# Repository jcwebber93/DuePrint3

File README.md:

# DuePrint3
Duet 3 to Stratasys PDB Interface Board. Used to convert a Stratasys Prodigy series printer (Dimension, uPrint, Fortus 250) to use a modern control board & firmware. This conversion is fully reversable (assuming the printer functions to begin with). Many thanks to AJ Quick and Archeantus (Jeremy) for their past efforts in detailing the electronics of the Dimension/uPrint machines, as well as sharing details on their Duet 2 WiFi conversions.
* https://wiki.cnc.xyz/Stratasys_uPrint_Retrofit
* https://forum.duet3d.com/topic/12647/another-stratasys-uprint-retrofit

[Additional details for this project on the Duet3D forums.](https://forum.duet3d.com/topic/37434/dueprint-with-a-duet-3-6hc-stratasys-dimension-conversion)

At present, the implementation focuses on the Dimension 1200es printers (the implementations linked above focus on the uPrint series, which is quite similar. The electronics are laid out a touch differently, meaning the layout of the new hardware must change, as well where the stepper motor wiring taps in to the existing harness). The Duet 3 Mainboard 6HC, as well as the DP3EXB module (natively running RepRapFirmware/Duet3Expansion) interface with 17 inputs, and 11 outputs.
### Inputs
|Device|RRF Pin Name|Function|Gcode|Dependancy|Note|
|---|---|---|---|---|---|
|6HC HEADER 7|io2.in|PRINT BED TOUCH PR LIM SW|`M558 P5 H5 F1200:200 T18000 A3 C"!io2.in" ; Z probe`||Used for Z probing|
|6HC HEADER 9|io6.in|Z-AXIS EOT|`M574 Z2 S1 P"!io6.in" ; Z EOT to Z endstop on high side`||Remapped as part of Z homing routine|
|6HC HEADER 11|io4.in|Y-AXIS EOT|`M950 J6 C"!io4.in" ; Y EOT (High, Back)`||Used for Y end of travel (high side, back of printer)|
|6HC HEADER 13|io3.in|X-AXIS EOT|`M950 J5 C"!io3.in" ; X EOT (High)`||Used for X end of travel|
|6HC HEADER 15|io0.in|X-AXIS HOME SW|`M574 X1 S1 P"!io0.in" ; X home limit (low side)`||Used for X homing (low side)|
|6HC HEADER 17|io1.in|Y-AXIS HOME SW|`M574 Y1 S1 P"!io1.in" ; Y home limit (low side, front of printer)`||Used for Y homing (low side, front of printer)|
|6HC HEADER 19|io5.in|Z-AXIS HOME SW|`M950 J7 C"!io5.in" ; Z Home`||Remapped as part of Z homing routine|
|6HC HEADER 21|io8.in|POWER I/O|`M950 J11 C"io8.in" ; Power Switch Status`||Front power switch status|
|6HC HEADER 23|io7.in|PRINT HEAD TEMP ALARM|`M950 J9 C"!io7.in" ; Print Head Temp Alarm`||Print head temperature alarm|
|DP3EXB |PA07|CHAMBER TEMP ALARM|`M950 J10 C"124.pa07" ; Chamber Temp Alarm`||Chamber temperature alarm|
|DP3EXB |PA06|HEAD THERMOSTAT STATUS|`M950 J1 C"124.pa06" ; Head Thermostat`||Head thermostat|
|DP3EXB |PA05|DOOR SWITCH|`M950 J2 C"124.pa05" ; Door Status`||Door switch status|
|DP3EXB |PA04|SUPPORT TOGGLE SW|`M950 J3 C"124.pa04" ; T1 Toggle`||T1 (Support) toggle sensor|
|DP3EXB |PB11|MODEL TOGGLE SW|`M950 J4 C"124.pb08" ; T0 toggle`||T0 (Model) toggle sensor|
|6HC HEADER 18&20|temp0&VSSA|CHAMBER THERM|`M308 S0 A"Chamber" P"temp0" Y"linear-analog" F0 B-42 C113 ; Chamber Temp Sensor`||Chamber temperature sensor|
|6HC HEADER 22&24|temp2&VSSA|SUPPORT THERM|`M308 S1 A"Model" P"temp1" Y"linear-analog" F0 B12.5 C328 ; T1 (Support) Temp Sensor`||Tool 1 (Support) temperature sensor|
|6HC HEADER 26&28|temp1&VSSA|MODEL THERM|`M308 S2 A"Support" P"temp2" Y"linear-analog" F0 B12.5 C328 ; T0 (Model) Temp Sensor`||Tool 0 (Model) temperature sensor|

### Outputs
|Device|RRF Pin Name|Function|Gcode|Dependancy|Note|
|---|---|---|---|---|---|
|6HC HEADER 2|io0.out|120V ON|`M950 P5 C"io0.out" ; 120V On`|Outputs need to be enabled via "M42 P7 S0"|Enables 120V power supplies|
|6HC HEADER 3|out4|48V RTN|`M950 P7 C"!out4"  ; Disable Outputs`||This provides power to DuePrint3 level shifters.|
|6HC HEADER 4|io1.out|POWER ON|`M950 P6 C"io1.out" ; Controlled Shutdown`|Outputs need to be enabled via "M42 P7 S0"|When enabled, allows the printer to handle a controlled shutdown when front power switch is toggled|
|6HC HEADER 6|io3.out|MOTOR ENA|`M950 P1 C"io3.out" ;Extruder Motor`|Outputs need to be enabled via "M42 P7 S0"|Enables the extruder motor|
|6HC HEADER 8|io4.out|CHAMBER HEATER ENA|`M950 H0 C"io4.out" T0 ; Chamber heater, Sensor 0`|Outputs need to be enabled via "M42 P7 S0"|Chamber heater|
|6HC HEADER 10|io2.out|BLOWER ENA|`M950 P0 C"io2.out" ; Head Blower Fan`|Outputs need to be enabled via "M42 P7 S0"|Used to enable or disable head blower fan|
|6HC HEADER 12|io7.out|SUPPORT HEATER ENA|`M950 H2 C"io7.out" T2 ; T1 heater, Sensor 2`|Outputs need to be enabled via "M42 P7 S0"|Tool 1 (Support) heater|
|6HC HEADER 14|io5.out|EXTRUDER MODEL HEATER ENA|`M950 H1 C"io5.out" T1 ; T0 heater, Sensor 1`|Outputs need to be enabled via "M42 P7 S0"|Tool 0 (Model) heater|
|6HC HEADER 16|io6.out|DOOR SOLENOID ENA|`M950 P3 C"io6.out" ; Door Lock`|Outputs need to be enabled via "M42 P7 S0"|Used to enable or disable the door lock|
|DP3EXB |PA08|LED LIGHTS ENA|`M950 P4 C"124.pa24" ; Chamber Lights`||Used to enable or disable chamber lights|
|DP3EXB |PA10|PRINT BED TOUCH PR ENA|`M950 P2 C"124.pa25" ;Doesn't seem to function?`||Does not seem to have a function|

### Other
|Header Pin|Desc.|Label|
|---|---|---|
|6HC HEADER 1|N/A|NC|
|6HC HEADER 5|N/A|48V|
|6HC HEADER 25|N/A|NC|
|6HC HEADER 27|N/A|5V|
|6HC HEADER 29|N/A|GND|
|6HC HEADER 30|N/A|GND|

### Spares Header
|Header Pin|Desc.|Label|
|---|---|---|
|SPARE 1||GND|
|SPARE 2|PA27|SPR4|
|SPARE 3|PA02|SPR1|
|SPARE 4|PA23|SPR3|
|SPARE 5|PA01|SPR2|
|SPARE 6|PA19|I_SPR2|
|SPARE 7|PA12|I_SPR1|
|SPARE 8|PA17|SPR5|
|SPARE 9||5V|
|SPARE 10|PA09|SPR6|
|SPARE 11||GND|
|SPARE 12|PA11|SPR7|
|SPARE 13||12V|
|SPARE 14|PA18|SPR8|

The 6HC directly drives the X, Y, and Z stepper motors (vs. controlling them through the Stratasys PDB). The 6HC, unlike the Duet2 (and Duex boards) does not natively have STEP/DIR pins used to emit step and direction pulses. Instead, a DP3EXB expansion board running a fork of Duet3Expansion is used to natively control the extruder's closed loop DC motor. The extruder can be tuned via the ClosedLoopTuning plugin for DWC, with the motor parameters being configured in Config.g. RRF is able to monitor the motor for position errors.

## Materials
[A detailed BOM can be found here](https://github.com/jcwebber93/DuePrint3/blob/v2.5.0/DuePrint3%20BOM.xlsx), with the approximate cost being ~$660 (60% of this is Duet3D 6HC, DP3EXB Module, and DuetScreen).

## Interface Board Design
[The KidCad project for the DuePrint3 board can be found here](https://github.com/jcwebber93/DuePrint3/tree/v2.5.0/DuePrint3%20KiCad%20Project)

## Wiring
[A detailed wire list can be found here.](https://github.com/jcwebber93/DuePrint3/blob/v2.5.0/DuePrint3%20Wire%20List.xlsx) Connectors & crimps for the Duet 3 6HC are supplied with the board, but are JST VH (stepper motors) and Molex KK / Wurth WR-WTB (Wurth connectors/contacts are supplied with Duet Boards). The interface board 6HC and spares header are JST PHD, and spare 5v and 12v headers are Molex Micro-3.0 series connectors & crimps. The headers for the PBD ribbon cables are Samtec EHT series headers.

## DP3EXB Prep
DP3EXB prep to detailed

## Interface Board Prep
If the Interface Board (w/Sammy-C21) is the only CAN-FD device, aside from the Duet 3 6HC, place a 2-socket jumper on J13 as indicated to enable the CAN-FD termination resistor.

J11 connects to the 6HC. J12 can be used with additional expansion boards (such as a Duet 3 SZP on the print head, which could be used as an accelerometer or for bed scanning), provided the CAN-FD bus is terminated on the additional board.

## RepRapFirmware Prep
At present, the 6HC and DP3EXB are running a fork of 3.6.3 (to be documented). [Configuration files are located here](https://github.com/jcwebber93/DuePrint3/tree/v2.0.0/Duet%203%20Configuration/System%20Directory), and [Macros are located here.](https://github.com/jcwebber93/DuePrint3/tree/v2.0.0/Duet%203%20Configuration/Macros%20Directory)

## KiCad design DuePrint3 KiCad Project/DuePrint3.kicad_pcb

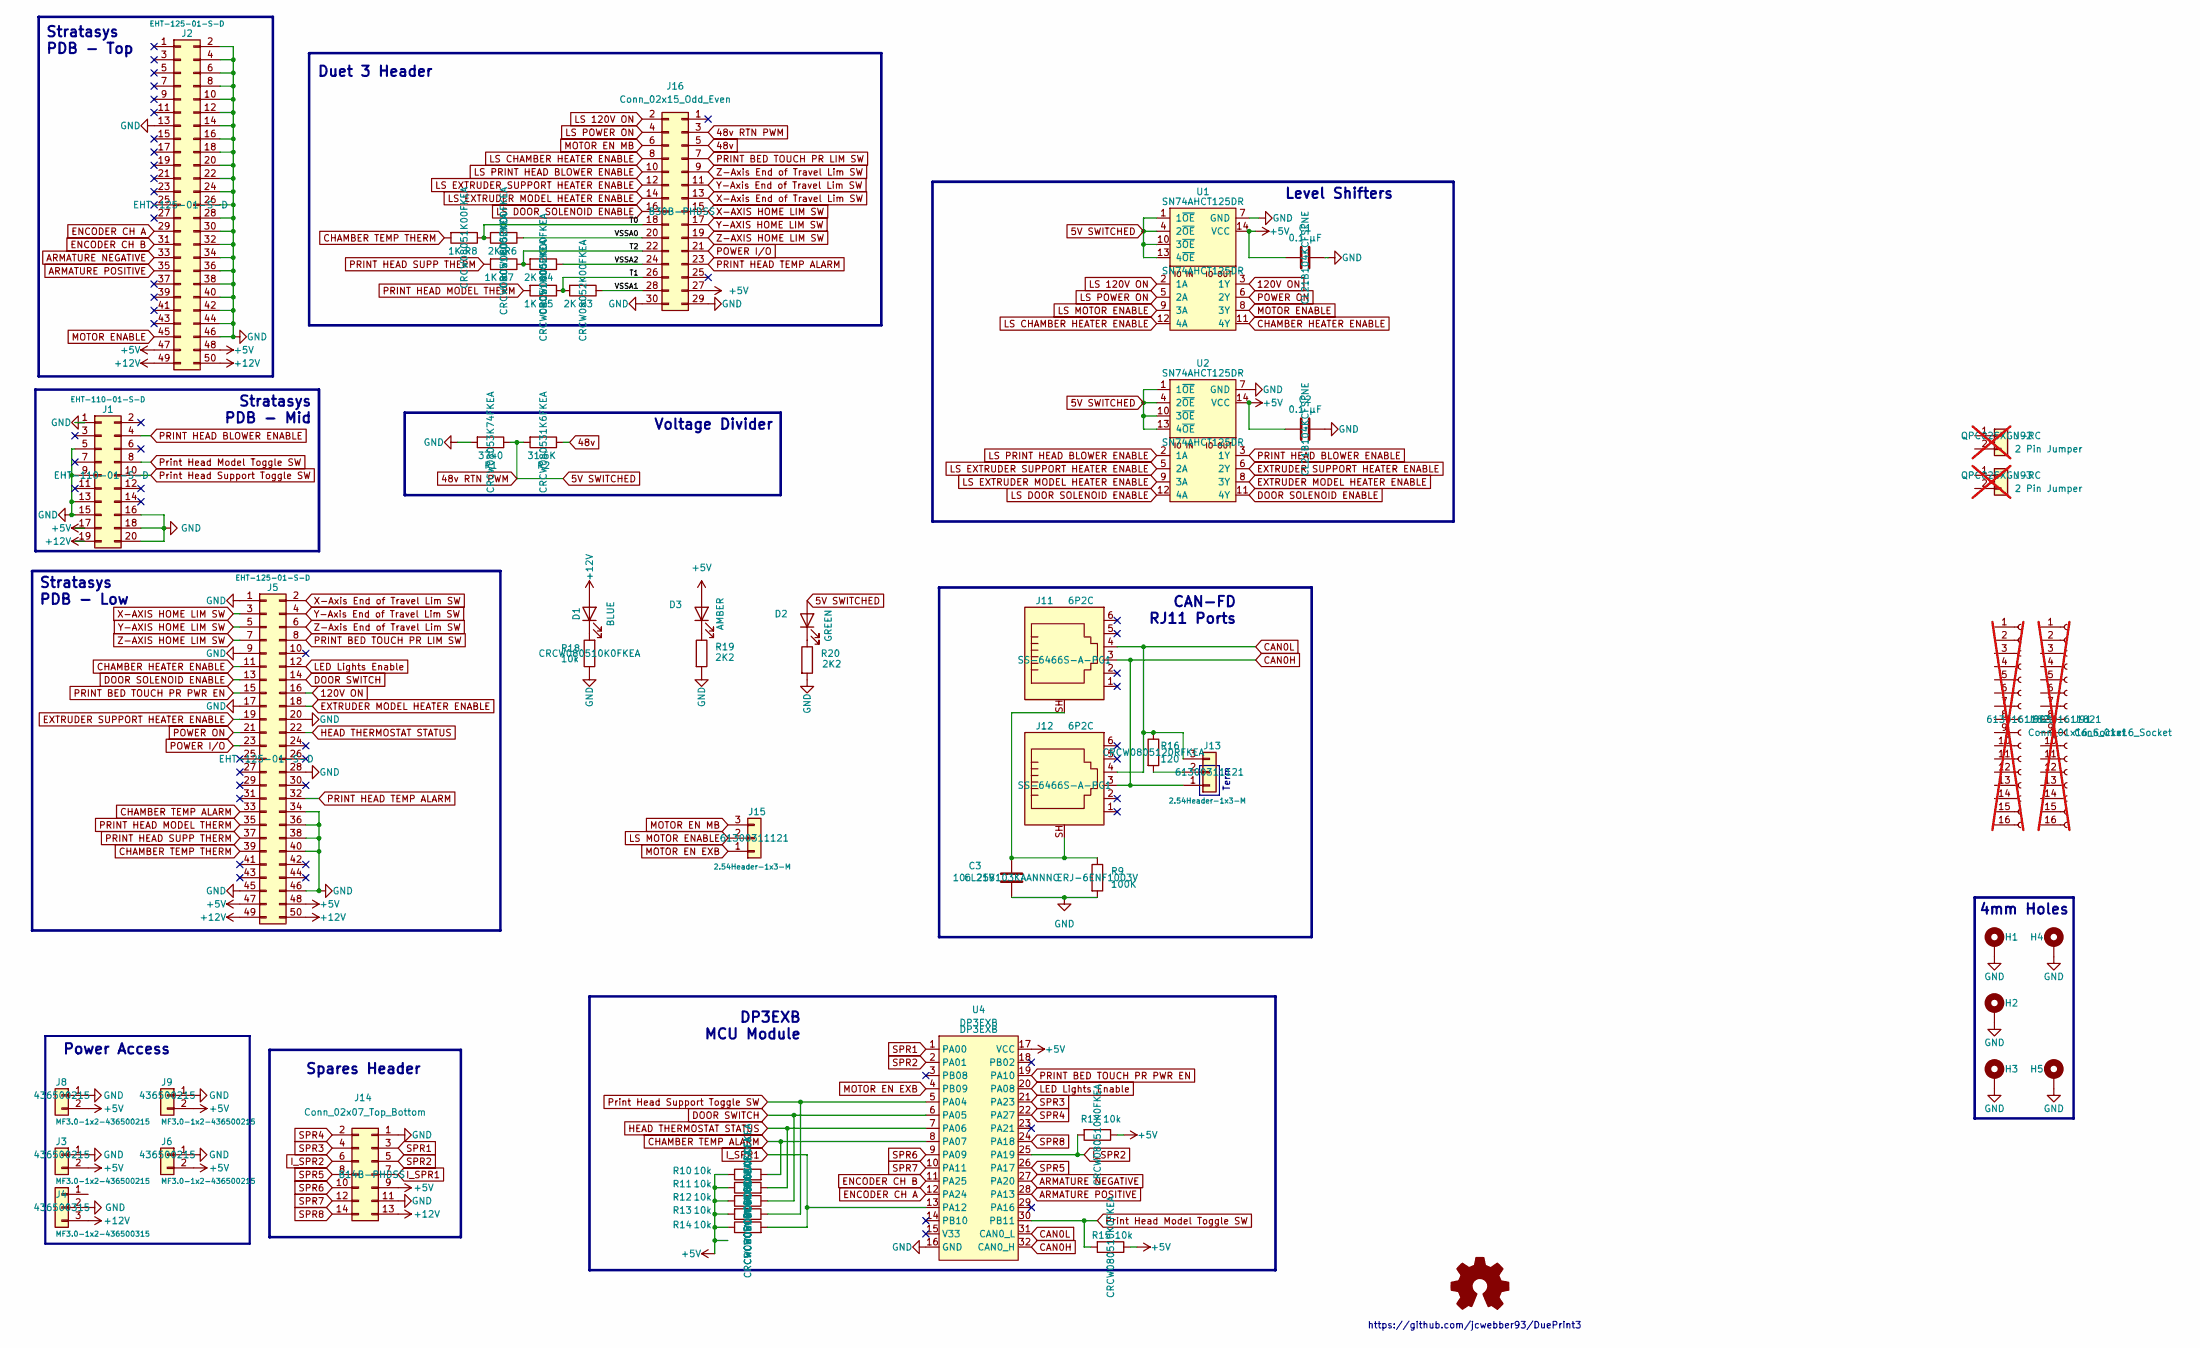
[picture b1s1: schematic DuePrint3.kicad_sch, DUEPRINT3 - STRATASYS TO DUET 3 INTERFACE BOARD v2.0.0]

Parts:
C1, C2: 0.1 µF; C_0805_2012Metric_Pad1.18x1.45mm_HandSolder; Part Number CL21B104KCFSFNE
C3: 10n 25V; C_0805_2012Metric_Pad1.18x1.45mm_HandSolder; Part Number CL21B103KAANNNC
D1: 12V; LED_0805_2012Metric_Pad1.15x1.40mm_HandSolder; Part Number 150080BS75000
D2: 5V_SW; LED_0805_2012Metric_Pad1.15x1.40mm_HandSolder; Part Number 150080VS75000
D3: 5V; LED_0805_2012Metric_Pad1.15x1.40mm_HandSolder; Part Number 150080AS75000
H1, H2, H3, H4, H5: MountingHole_Pad; MountingHole_4.00mm_Pad
J1: EHT-110-01-S-D; EHT-110-01-XX-D; Part Number EHT-110-01-S-D
J2, J5: EHT-125-01-S-D; SAMTEC_EHT-125-01-S-D; Part Number EHT-125-01-S-D
J3, J6, J8, J9: MF3.0-1x2-436500215; Molex_Micro-Fit_3.0_43650-0215_1x02_P3.00mm_Vertical; Part Number 436500215
J4: MF3.0-1x2-436500315; Molex_Micro-Fit_3.0_43650-0315_1x03_P3.00mm_Vertical; Part Number 436500315
J11, J12: 6P2C; BEL_SS-6466S-A-PG1; Part Number SS-6466S-A-PG1
J13, J15: 2.54Header-1x3-M; PinHeader_1x03_P2.54mm_Vertical; Part Number 61300311121
J14: Conn_02x07_Top_Bottom; JST_PHD_B14B-PHDSS_2x07_P2.00mm_Vertical; Part Number B14B-PHDSS
J16: Conn_02x15_Odd_Even; JST_PHD_B30B-PHDSS_2x15_P2.00mm_Vertical; Part Number B30B-PHDSS
J90, J91: Conn_01x16_Socket; PinHeader_1x16_P2.54mm_Vertical; Part Number 61301611821; not fitted
J92, J93: 2 Pin Jumper; Part Number QPC02SXGN-RC; not fitted
R1: 3740; R_0805_2012Metric_Pad1.20x1.40mm_HandSolder; Part Number CRCW08053K74FKEA
R2: 31.6K; R_0805_2012Metric_Pad1.20x1.40mm_HandSolder; Part Number CRCW080531K6FKEA
R3, R4, R6: 2K; R_0805_2012Metric_Pad1.20x1.40mm_HandSolder; Part Number CRCW08052K00FKEA
R5, R7, R8: 1K; R_0805_2012Metric_Pad1.20x1.40mm_HandSolder; Part Number CRCW08051K00FKEA
R9: 100K; R_0805_2012Metric_Pad1.20x1.40mm_HandSolder; Part Number ERJ-6ENF1003V
R10, R11, R12, R13, R14, R15, R17, R18: 10k; R_0805_2012Metric_Pad1.20x1.40mm_HandSolder; Part Number CRCW080510K0FKEA
R16: 120; R_0805_2012Metric_Pad1.20x1.40mm_HandSolder; Part Number CRCW0805120RFKEA
R19, R20: 2K2; R_0805_2012Metric_Pad1.20x1.40mm_HandSolder; Part Number CRCW08052K20FKEA; LCSC Part # C413087
U1, U2: SN74AHCT125DR; SOIC-14_3.9x8.7mm_P1.27mm; Part Number SN74AHCT125DR
U4: DP3EXB; Part Number DP3EXB

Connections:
48v: J16.5, R2.1
48v RTN PWM: D2.2 (A), J16.3, R1.1, R2.2, U1.1 (1~OE), U1.4 (2~OE), U1.10 (3~OE), U1.13 (4~OE), U2.1 (1~OE), U2.4 (2~OE), U2.10 (3~OE), U2.13 (4~OE)
120V ON: J5.16, U1.3 (1Y)
+5V: C1.1, C2.1, D3.2 (A), J1.17, J2.47, J2.48, J3.2, J5.47, J5.48, J6.2, J8.2, J9.2, J14.9, J16.27, R10.1, R11.1, R12.2, R13.2, R14.1, R15.1, R17.1, U1.14 (VCC), U2.14 (VCC), U4.17 (VCC)
+12V: D1.2 (A), J1.19, J2.49, J2.50, J4.3, J5.49, J5.50, J14.13
/T0: J16.18, R6.2, R8.1
/T1: J16.26, R3.2, R5.1
/T2: J16.22, R4.2, R7.1
/VSSA0: J16.20, R6.1
/VSSA1: J16.28, R3.1
/VSSA2: J16.24, R4.1
ARMATURE NEGATIVE: J2.33, U4.27 (PA20)
ARMATURE POSITIVE: J2.35, U4.28 (PA13)
CAN0H: J11.3, J12.3, J13.1, U4.32 (CAN0_H)
CAN0L: J11.4, J12.4, J13.3, R16.1, U4.31 (CAN0_L)
CHAMBER HEATER ENABLE: J5.11, U1.11 (4Y)
CHAMBER TEMP ALARM: J5.33, R10.2, U4.8 (PA07)
CHAMBER TEMP THERM: J5.39, R8.2
DOOR SOLENOID ENABLE: J5.13, U2.11 (4Y)
DOOR SWITCH: J5.14, R12.1, U4.6 (PA05)
ENCODER CH A: J2.29, U4.12 (PA24)
ENCODER CH B: J2.31, U4.11 (PA25)
EXTRUDER MODEL HEATER ENABLE: J5.18, U2.8 (3Y)
EXTRUDER SUPPORT HEATER ENABLE: J5.19, U2.6 (2Y)
GND: C1.2, C2.2, C3.2, H1.1, H2.1, H3.1, H4.1, H5.1, J1.1, J1.5, J1.9, J1.13, J1.15, J1.16, J1.18, J1.20, J2.2, J2.4, J2.6, J2.8, J2.10, J2.12, J2.13, J2.14, J2.16, J2.18, J2.20, J2.22, J2.24, J2.26, J2.28, J2.30, J2.32, J2.34, J2.36, J2.38, J2.40, J2.42, J2.44, J2.46, J3.1, J4.2, J5.1, J5.9, J5.17, J5.20, J5.28, J5.34, J5.36, J5.38, J5.40, J5.45, J5.46, J6.1, J8.1, J9.1, J14.1, J14.11, J16.29, J16.30, R1.2, R9.2, R18.1, R19.2, R20.2, U1.7 (GND), U2.7 (GND), U4.16 (GND)
HEAD THERMOSTAT STATUS: J5.22, R11.2, U4.7 (PA06)
I_SPR1: J14.7, R14.2, U4.13 (PA12)
I_SPR2: J14.6, R17.2, U4.25 (PA19)
LED Lights Enable: J5.12, U4.20 (PA08)
LS 120V ON: J16.2, U1.2 (1A)
LS CHAMBER HEATER ENABLE: J16.8, U1.12 (4A)
LS DOOR SOLENOID ENABLE: J16.16, U2.12 (4A)
LS EXTRUDER MODEL HEATER ENABLE: J16.14, U2.9 (3A)
LS EXTRUDER SUPPORT HEATER ENABLE: J16.12, U2.5 (2A)
LS MOTOR ENABLE: J15.2, U1.9 (3A)
LS POWER ON: J16.4, U1.5 (2A)
LS PRINT HEAD BLOWER ENABLE: J16.10, U2.2 (1A)
MOTOR EN EXB: J15.1, U4.4 (PB09)
MOTOR EN MB: J15.3, J16.6
MOTOR ENABLE: J2.45, U1.8 (3Y)
unnamed: C3.1, J11.SH, J12.SH, R9.1
unnamed: D1.1 (K), R18.2
unnamed: D2.1 (K), R20.1
unnamed: D3.1 (K), R19.1
unnamed: J13.2, R16.2
POWER I/O: J5.23, J16.21
POWER ON: J5.21, U1.6 (2Y)
PRINT BED TOUCH PR LIM SW: J5.8, J16.7
PRINT BED TOUCH PR PWR EN: J5.15, U4.19 (PA10)
PRINT HEAD BLOWER ENABLE: J1.4, U2.3 (1Y)
PRINT HEAD MODEL THERM: J5.35, R5.2
PRINT HEAD SUPP THERM: J5.37, R7.2
PRINT HEAD TEMP ALARM: J5.32, J16.23
Print Head Model Toggle SW: J1.8, R15.2, U4.30 (PB11)
Print Head Support Toggle SW: J1.10, R13.1, U4.5 (PA04)
SPR1: J14.3, U4.1 (PA00)
SPR2: J14.5, U4.2 (PA01)
SPR3: J14.4, U4.21 (PA23)
SPR4: J14.2, U4.22 (PA27)
SPR5: J14.8, U4.26 (PA17)
SPR6: J14.10, U4.9 (PA09)
SPR7: J14.12, U4.10 (PA11)
SPR8: J14.14, U4.24 (PA18)
X-AXIS HOME LIM SW: J5.3, J16.15
X-Axis End of Travel Lim SW: J5.2, J16.13
Y-AXIS HOME LIM SW: J5.5, J16.17
Y-Axis End of Travel Lim SW: J5.4, J16.11
Z-AXIS HOME LIM SW: J5.7, J16.19
Z-Axis End of Travel Lim SW: J5.6, J16.9

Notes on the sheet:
Duet 3 Header
4mm Holes
Stratasys PDB - Mid
CAN-FD RJ11 Ports
Level Shifters
Stratasys PDB - Low
Stratasys PDB - Top
https://github.com/jcwebber93/DuePrint3
Spares Header
Term
Voltage Divider
DP3EXB MCU Module
Power Access

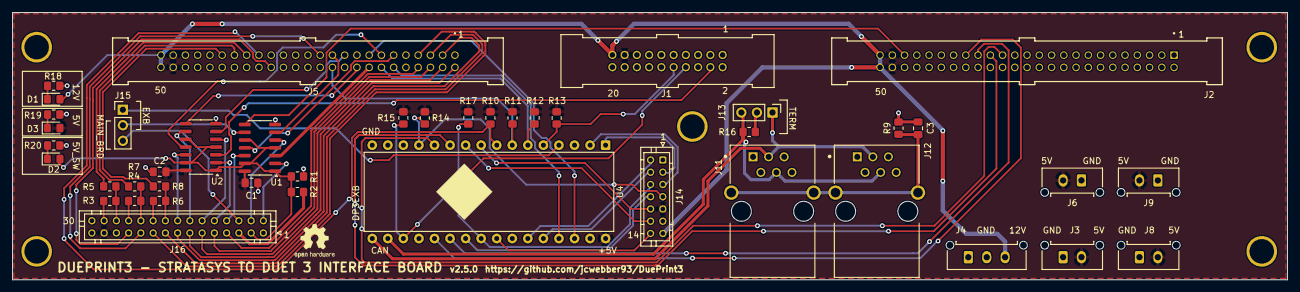
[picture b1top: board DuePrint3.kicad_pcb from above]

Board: 2 copper layers, 208.2 x 43.6 mm, 48 parts (0 on the bottom side), 69 nets.

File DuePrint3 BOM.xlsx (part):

|  |  |  |  | 459.93657600000034 |  | https://www.digikey.com/short/q54m7hm0
Item | Part Number | Description | Quantity | REF | Price | EXT Price | Note | Link
1 |  | Duet 3 Mainboard 6HC | 1 |  | 269.99 | 269.99 |  | https://www.filastruder.com/collections/duet3d/products/duet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
2 |  | DuePrint3 v2.5.0 PCB | 1 |  | 30 | 30
3 | LRS-75-48 | Power Suppy, AC/DC, 48V 75W | 1 |  | 14.1 | 14.1 |  | https://www.digikey.com/en/products/detail/mean-well-usa-inc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
4 | PAAD04010BH-0000 | Fan, 5V, 40x10, 0.25A | 2 | FAN 1, FAN 2 | 5.33 | 10.66 | The Stratasys 12V/5V PSU requires a minimum load of 0.7A on 5V, so a "dummy" lo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 | https://www.digikey.com/en/products/detail/boyd-laconia-llc/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
5 | CL21B103KAANNNC | 10nF, 25V X7R Cap, 0805 | 1 | C3 | 0.1 | 0.1 |  | https://www.digikey.com/en/products/detail/samsung-electro-m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
6 | CL21B104KCFSFNE | 0.1 uF, 100V X7R Cap, 0805 | 2 | C1,C2 | 0.1 | 0.2 |  | https://www.digikey.com/en/products/detail/samsung-electro-m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
7 | 150080BS75000 | LED, Blue, 0805 | 1 | D1 (12V) | 0.19 | 0.19 |  | https://www.digikey.com/en/products/detail/w%C3%BCrth-elektr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
8 | 150080VS75000 | LED, Green, 0805 | 1 | D2 (5V_SW) | 0.19 | 0.19 |  | https://www.digikey.com/en/products/detail/w%C3%BCrth-elektr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
9 | 150080AS75000 | LED, Amber, 0805 | 1 | D3 (5V) | 0.25 | 0.25 |  | https://www.digikey.com/en/products/detail/w%C3%BCrth-elektr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
10 | EHT-110-01-F-D | Conn, Header, 20 pos, EHT | 1 | J1 | 2.77 | 2.77 |  | https://www.digikey.com/en/products/detail/samtec-inc/EHT-11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
11 | 436500315 | Conn, Header, 3 pos, MicroFit- 3.0 | 1 | J4 | 1.1499999999999999 | 1.1499999999999999 |  | https://www.digikey.com/en/products/detail/molex/0436500315/283462
12 | B14B-PHDSS | Conn, Header, 14 pos, JST PHD, 2.0 | 1 | J14 | 0.47 | 0.47 |  | https://www.digikey.com/en/products/category/rectangular-con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
13 | B30B-PHDSS | Conn, Header, 30 pos, JST PHD, 2.0 | 1 | J16 | 0.86 | 0.86 |  | https://www.digikey.com/en/products/detail/jst-sales-america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
14 | SS-6466S-A-PG1 | Conn, 6p6c R/A, RJ11 | 2 | J11,J12 | 0.61 | 1.22 |  | https://www.digikey.com/en/products/detail/stewart-connector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
15 | 61300311121 | Conn, Header, 3 pos | 2 | J13,J15 | 0.13 | 0.26 | Can buy larger and cut down | https://www.digikey.com/en/products/detail/w%C3%BCrth-elektr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
16 | EHT-125-01-F-D | Conn, Header, 50 pos, EHT | 2 | J2,J5 | 6.91 | 13.82 |  | https://www.digikey.com/en/products/detail/samtec-inc/EHT-12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
17 | 436500215 | Conn, Header, 2 pos, MicroFit- 3.0 | 4 | J3,J6,J8,J9 | 0.89 | 3.56 |  | https://www.digikey.com/en/products/detail/molex/0436500215/283461
18 | 61301611821 | Conn, Header, 16 pos | 2 | J90,J91 | 0.61 | 1.22 |  | https://www.digikey.com/en/products/detail/w%C3%BCrth-elektr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
19 | QPC02SXGN-RC | Jumper, Shorting, 2 Pos | 2 | J92,J93 | 0.1 | 0.2 | For CAN-FD termination and Motor En select | https://www.digikey.com/en/products/detail/sullins-connector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
20 | CRCW08053K74FKEA | 3.74K Res, 1% 0.125W, 0805 | 1 | R1 | 0.1 | 0.1 |  | https://www.digikey.com/en/products/detail/vishay-dale/crcw0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
21 | CRCW080531K6FKEA | 31.6K Res, 1% 0.125W, 0805 | 1 | R2 | 0.1 | 0.1 |  | https://www.digikey.com/en/products/detail/vishay-dale/CRCW0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
22 | ERJ-6ENF1003V | 100K Res, 1% 0.125W, 0805 | 1 | R9 | 0.1 | 0.1 |  | https://www.digikey.com/en/products/detail/panasonic-industr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
23 | CRCW0805120RFKEA | 120 Res, 0805 | 1 | R16 | 0.1 | 0.1 |  | https://www.digikey.com/en/products/detail/vishay-dale/CRCW0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
24 | CRCW080510K0FKEA | 10K Res, 1% 0.25W, 0805 | 8 | R10,R11,R12,R13,R14,R15,R17,R18 | 0.1 | 0.8 |  | https://www.digikey.com/en/products/detail/vishay-dale/crcw0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
25 | CRCW08052K20FKEA | 2K2 | 2 | R19,R20 | 0.1 | 0.2 |  | https://www.digikey.com/en/products/detail/vishay-dale/CRCW0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
26 | CRCW08052K00FKEA | 2K Res, 1% 0.125W, 0805 | 3 | R3,R4,R6 | 0.1 | 0.30000000000000004 |  | https://www.digikey.com/en/products/detail/vishay-dale/CRCW0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
27 | CRCW08051K00FKEA | 1K Res, 1% 0.125W, 0805 | 3 | R5,R7,R8 | 0.1 | 0.30000000000000004 |  | https://www.digikey.com/en/products/detail/vishay-dale/CRCW0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
28 | DP3EXB | DP3EXB | 1 | U4 | 40 | 40
29 | SN74AHCT125DR | SN74AHCT125DR, 14-SOIC | 2 | U1,U2 | 0.4 | 0.8 |  | https://www.digikey.com/en/products/detail/texas-instruments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
30 | 39012086 | Conn, Plug, 8 pos, Mini-Fit Jr | 1 | P2 | 0.66 | 0.66 |  | https://www.digikey.com/en/products/detail/molex/0039012086/930285
31 | 39012205 | Conn, Rcpt, 20 pos, Mini-Fit Jr | 1 | P3 | 1.48 | 1.48 |  | https://www.digikey.com/en/products/detail/molex/0039012205/930279
32 | 39012206 | Conn, Plug, 20 pos, Mini-Fit Jr | 1 | P1 | 1.2 | 1.2 |  | https://www.digikey.com/en/products/detail/molex/0039012206/4693014
33 | 39000048 | Pin, 22-28 AWG, Mini-Fit Jr | 18 |  | 6.0999999999999999E-2 | 1.0979999999999999 |  | https://www.digikey.com/en/products/detail/molex/0039000048/1643437
34 | 39000046 | Socket, 22-28 AWG, Mini-Fit Jr | 6 |  | 5.1999999999999998E-2 | 0.312 |  | https://www.digikey.com/en/products/detail/molex/0039000046/1643436
35 | 430300010 | Socket, 26-30 AWG, Micro-Fit 3.0 | 4 |  | 0.2 | 0.8 |  | https://www.digikey.com/en/products/detail/molex/0430300010/252480
36 | 436450200 | Conn, Rcpt, 2 pos, Micro-Fit 3.0 | 2 | P8, P9 | 0.39 | 0.78 |  | https://www.digikey.com/en/products/detail/molex/0436450200/268974
37 | PHDR-30VS | Conn, Rcpt, 30 pos, JST PHD, 2.0 | 1 | P7 | 0.48 | 0.48 |  | https://www.digikey.com/en/products/detail/jst-sales-america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
38 | PHDR-14VS | Conn, Rcpt, 14 pos, JST PHD, 2.0 | 1 | Spares Header | 1.07 | 1.07 |  | https://www.digikey.com/en/products/detail/molex/0430251800/531407
39 | SPHD-002-P0.5 | Socket, 24-28 AWG, JST SPHD | 27 |  | 2.1000000000000001E-2 | 0.56700000000000006 |  | https://www.digikey.com/en/products/detail/jst-sales-america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
40 | VHR-4N | Conn, Rcpt, 4 pos, JST VH | 3 | P4,P5,P6 | 0.12 | 0.36 | Included in 6HC purchase | https://www.digikey.com/en/products/detail/jst-sales-america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
41 | SVH-21T-P1.1 | Socket, 18-22 AWG, JST VH | 12 |  | 0.12 | 1.44 | Included in 6HC purchase | https://www.mouser.com/ProductDetail/JST-Commercial/SVH-21T-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
42 | 61900511621 | Conn, Rcpt, 5 pos, WR-WTB | 9 | IO_0 IO_1 IO_2 IO_3 IO_4 IO_5 IO_6 IO_7 IO_8 | 0.17 | 1.53 | Included in 6HC purchase | https://www.digikey.com/en/products/detail/w%C3%BCrth-elektr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
43 | 61900211621 | Conn, Rcpt, 2 pos, WR-WTB | 3 | TEMP0 TEMP1 TEMP2 | 0.13 | 0.39 | Included in 6HC purchase | https://www.digikey.com/en/products/detail/w%C3%BCrth-elektr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
44 | 61900411621 | Conn, Rcpt, 4 pos, WR-WTB | 1 | OUT4 | 0.17 | 0.17 | Included in 6HC purchase | https://www.digikey.com/en/products/detail/w%C3%BCrth-elektr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
45 | 61900113722DEC | Socket, 22-28 AWG, WR-WTB | 28 |  | 0.15 | 4.2 | Included in 6HC purchase | https://www.digikey.com/en/products/detail/w%C3%BCrth-elektr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
46 | 350570-1 | Socket, 18-24 AWG, MATE-N-LOK | 6 |  | 6.6000000000000003E-2 | 0.39600000000000002 |  | https://www.digikey.com/en/products/detail/te-connectivity-a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
47 | 350536-1 | Socket, 14-20 AWG, MATE-N-LOK | 3 |  | 5.8999999999999997E-2 | 0.17699999999999999 |  | https://www.digikey.com/en/products/detail/te-connectivity-a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
48 | 350218-1 | Pin, 14-20 AWG, MATE-N-LOK | 6 |  | 5.8999999999999997E-2 | 0.35399999999999998 |  | https://www.digikey.com/en/products/detail/te-connectivity-a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
49 | 350561-1 | Pin, 18-24 AWG, MATE-N-LOK | 3 |  | 5.8999999999999997E-2 | 0.17699999999999999 |  | https://www.digikey.com/en/products/detail/te-connectivity-a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
50 | 350720-1 | Conn, Plug, 9 pos, MATE-N-LOK | 1 | P10 | 0.83 | 0.83 |  | https://www.digikey.com/en/products/detail/te-connectivity-a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
51 | 350782-1 | Conn, Rcpt, 9 pos, MATE-N-LOK | 1 | P11 | 0.51 | 0.51 |  | https://www.digikey.com/en/products/detail/te-connectivity-a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
52 | 130517 | Spade Terminal, 16-22 AWG, M4 | 10 |  | 0.43 | 4.3 | M4 or #8 stud, sized for your wires connecting VAC and VDC to 48VDC and 6HC | https://www.digikey.com/en/products/detail/te-connectivity-a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
53 |  | RJ11 connectors |  |  |  | 0 | In case custom length/custom purpose CAN-FD cables are desired
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
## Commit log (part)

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2026-02-07 v2.2.0 initial release
    Primarily focused on KiCad files, configuration files, build instructions.
